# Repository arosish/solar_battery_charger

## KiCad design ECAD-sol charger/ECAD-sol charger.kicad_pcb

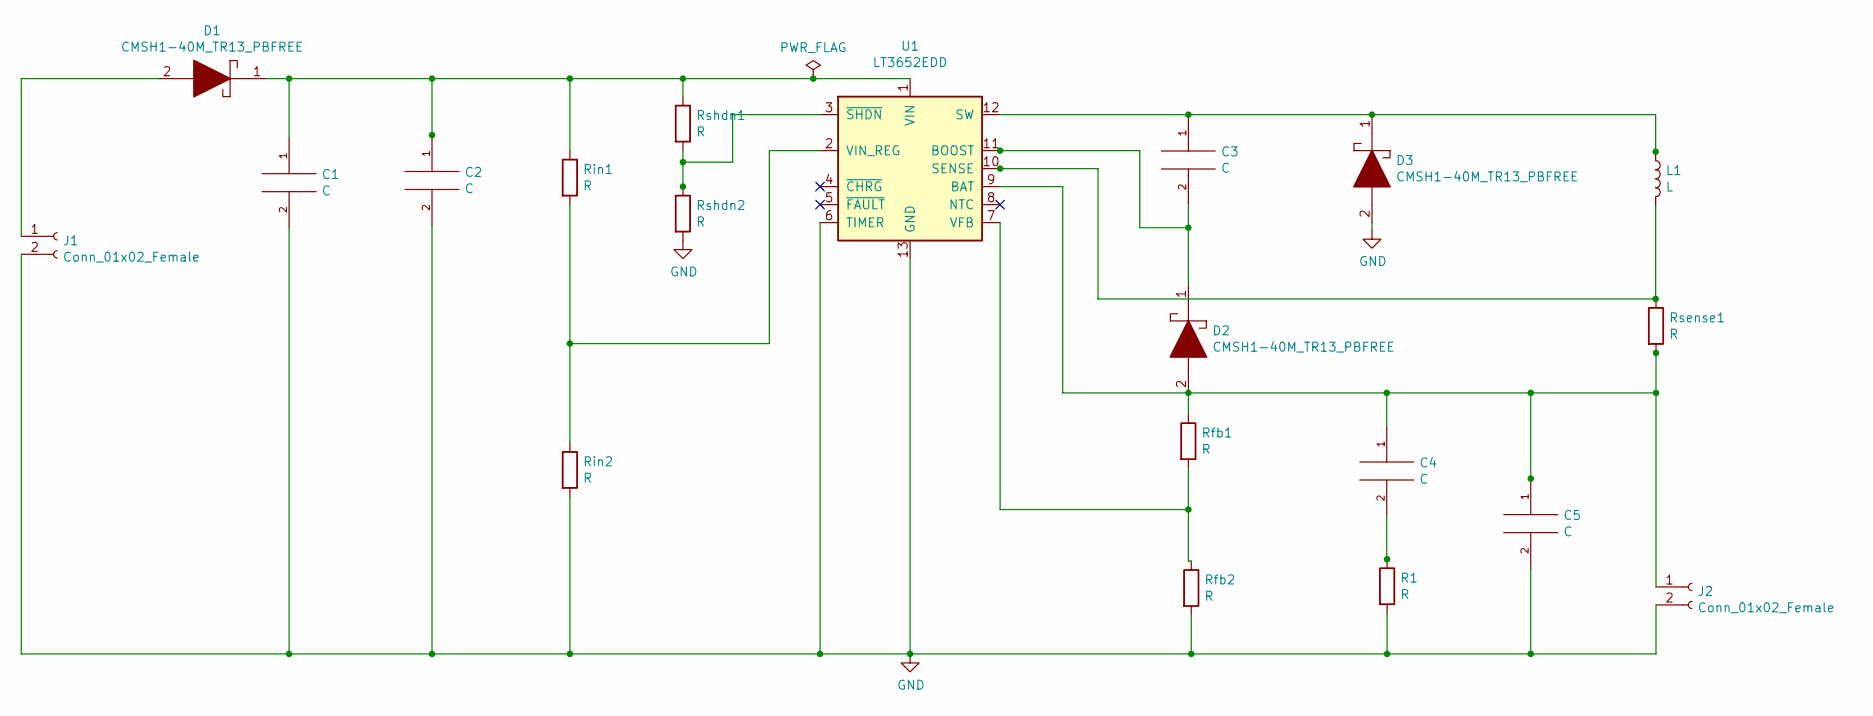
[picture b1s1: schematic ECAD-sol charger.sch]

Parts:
C1, C2, C3, C4, C5: C; C_Rect_L7.0mm_W2.0mm_P5.00mm
D1, D2, D3: CMSH1-40M_TR13_PBFREE; DIOM5226X262N; Manufacturer_Part_Number CMSH1-40M TR13 PBFREE; Mouser Part Number 610-CMSH1-40M/R
J1, J2: Conn_01x02_Female; PinSocket_1x02_P1.27mm_Vertical
L1: L; L_Axial_L6.6mm_D2.7mm_P10.16mm_Horizontal_Vishay_IM-2
R1: R; R_Axial_DIN0207_L6.3mm_D2.5mm_P7.62mm_Horizontal
Rfb1, Rfb2: R; R_Axial_DIN0207_L6.3mm_D2.5mm_P7.62mm_Horizontal
Rin1, Rin2: R; R_Axial_DIN0207_L6.3mm_D2.5mm_P7.62mm_Horizontal
Rsense1: R; R_Axial_DIN0207_L6.3mm_D2.5mm_P7.62mm_Horizontal
Rshdn1, Rshdn2: R; R_Axial_DIN0207_L6.3mm_D2.5mm_P7.62mm_Horizontal
U1: LT3652EDD; DFN-12-1EP_3x3mm_P0.45mm_EP1.66x2.38mm

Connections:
GND: C1.2, C2.2, C5.2, D3.2, J1.2, J2.2, R1.2, Rfb2.2, Rin2.2, Rshdn2.2, U1.6 (TIMER), U1.13 (GND)
unnamed: C1.1, C2.1, D1.1, Rin1.1, Rshdn1.1, U1.1 (VIN)
unnamed: C3.1, D3.1, L1.1, U1.12 (SW)
unnamed: C3.2, D2.1, U1.11 (BOOST)
unnamed: C4.1, C5.1, D2.2, J2.1, Rfb1.1, Rsense1.2, U1.9 (BAT)
unnamed: C4.2, R1.1
unnamed: D1.2, J1.1
unnamed: L1.2, Rsense1.1, U1.10 (SENSE)
unnamed: Rfb1.2, Rfb2.1, U1.7 (VFB)
unnamed: Rin1.2, Rin2.1, U1.2 (VIN_REG)
unnamed: Rshdn1.2, Rshdn2.1, U1.3 (~SHDN)

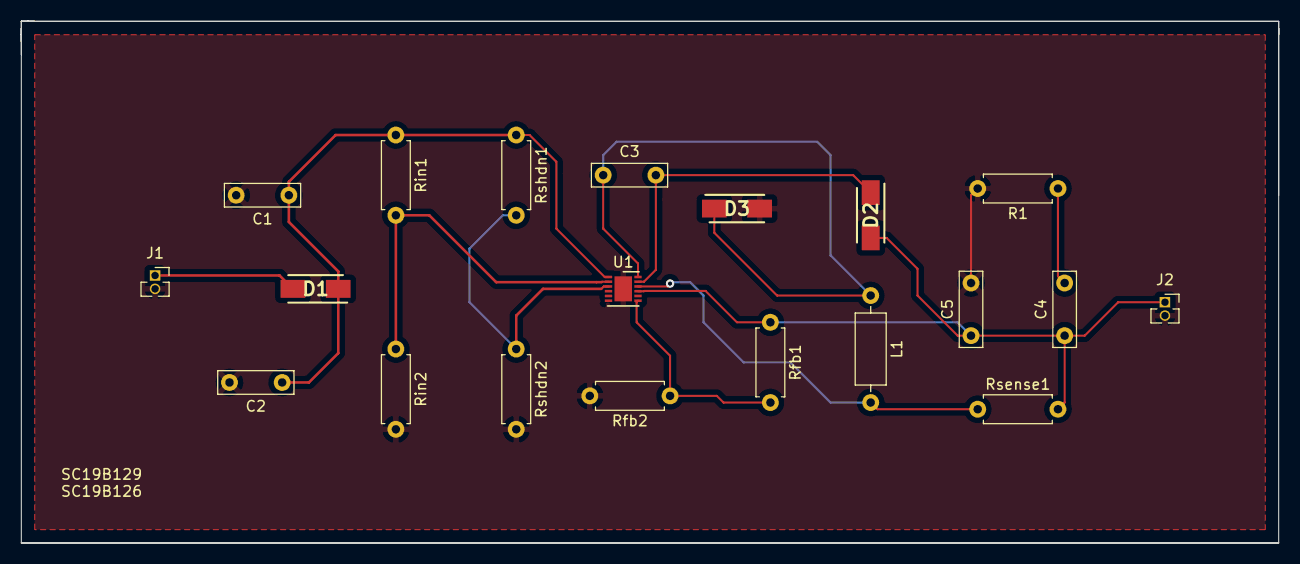
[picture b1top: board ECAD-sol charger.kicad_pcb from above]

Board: 2 copper layers, 119.4 x 49.5 mm, 20 parts (0 on the bottom side), 11 nets.
